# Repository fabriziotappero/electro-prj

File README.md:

# electronic projects
Bunch of electronics projects, pcb designs and embedded systems. All done in *KiCad*.

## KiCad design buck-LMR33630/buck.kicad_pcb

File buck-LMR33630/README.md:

This is a clever battery pack for a smartphone. It allows a 2S Sony NP battery 
to be interfaced with the standard USB-C port.

This pack includes a 5V, 3A Buck DC/DC Converter based on the TI LMR33630 and
a 19V, 2A step up converter based on the TI LM62421 as well.

The charging IC is the 

For any enquiry contact:

    fabrizio.tappero@gmail.com

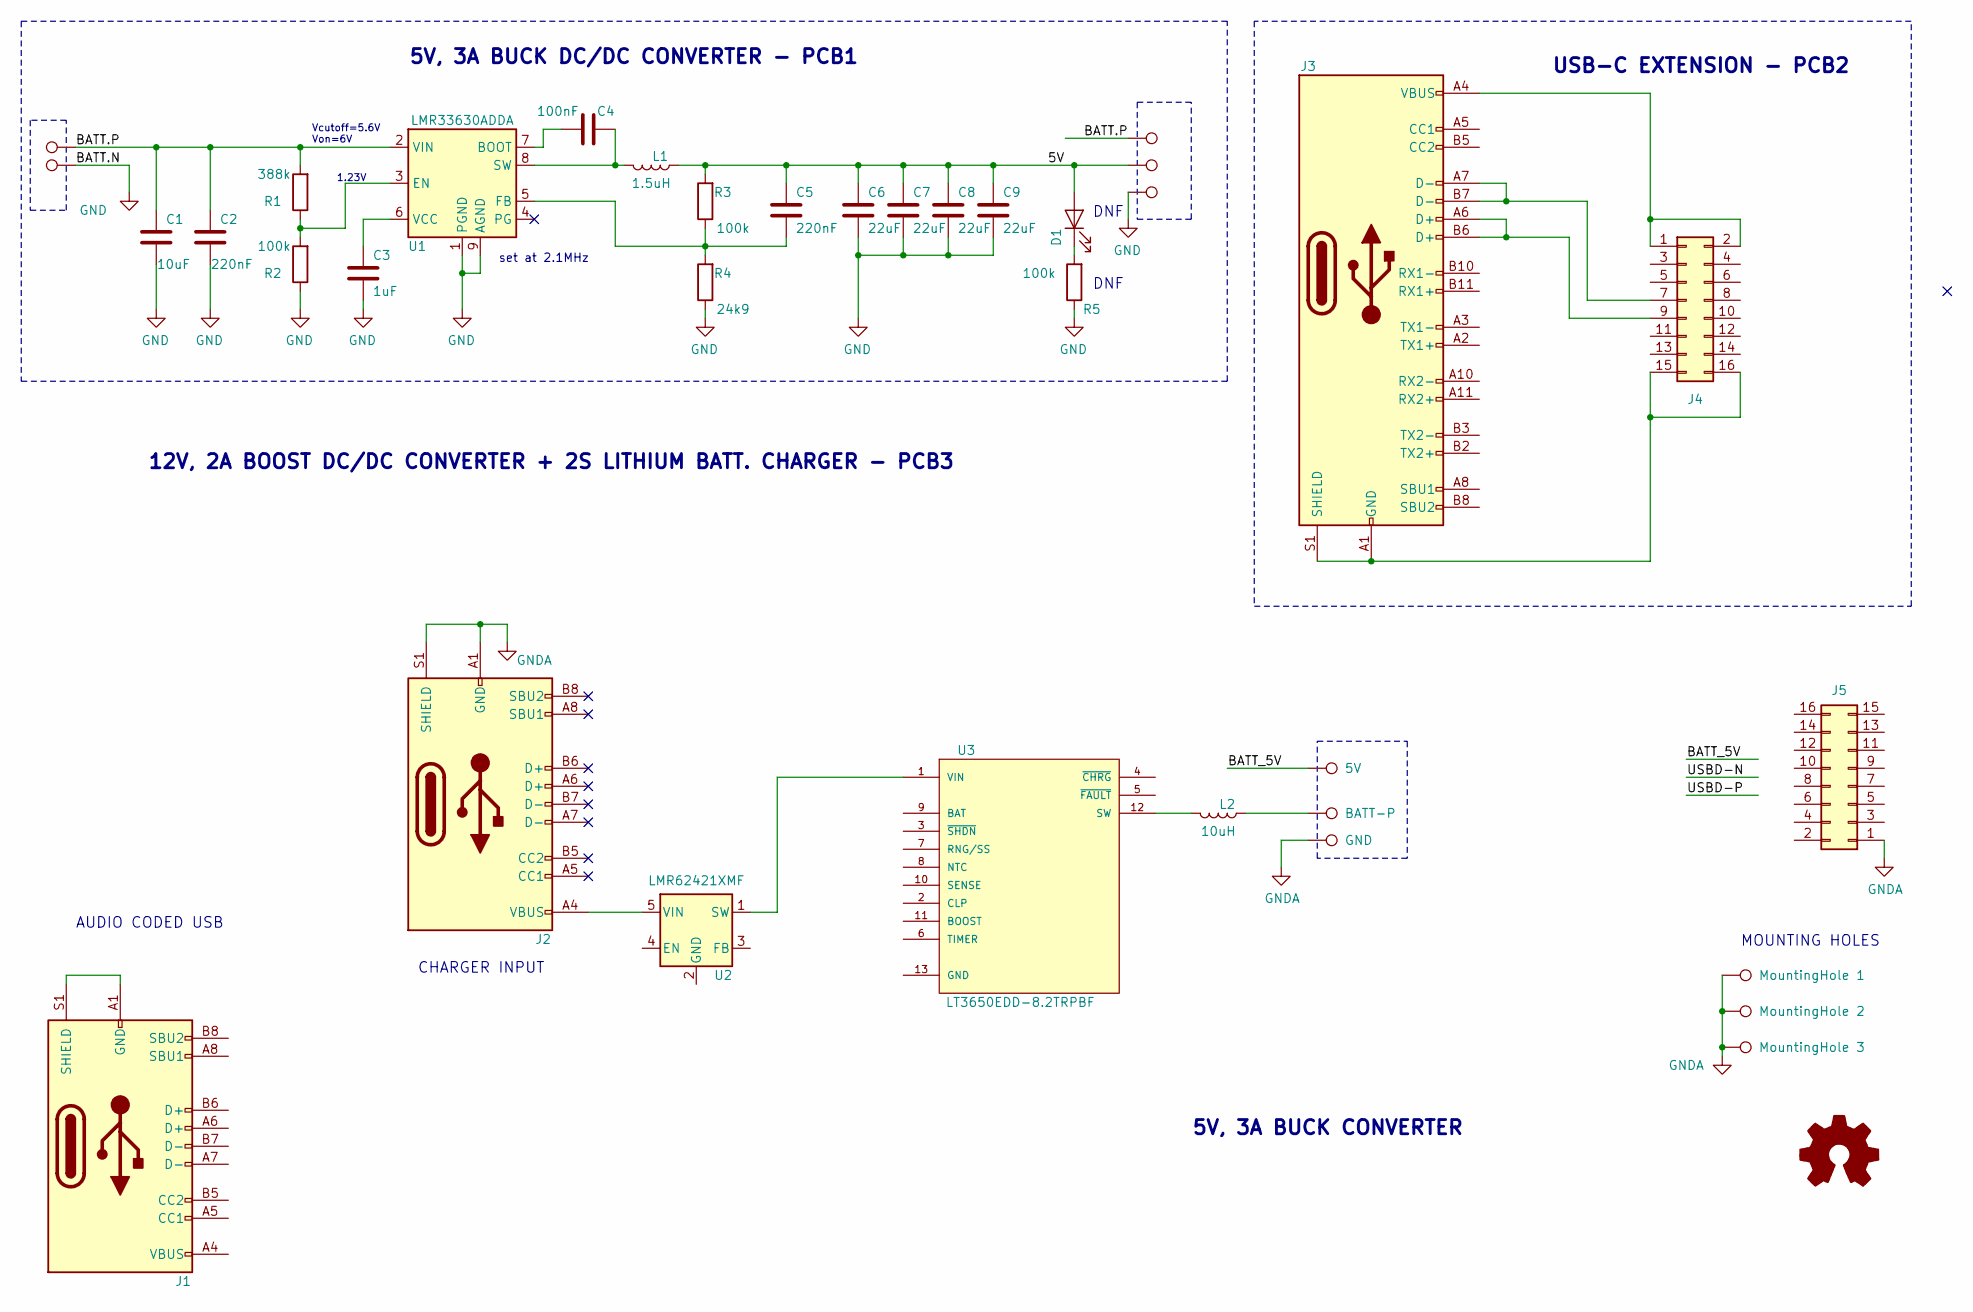
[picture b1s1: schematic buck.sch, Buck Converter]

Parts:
C1: 10uF; C_0805_2012Metric_Pad1.15x1.40mm_HandSolder; MPN TMK212BBJ106MGHT; Digikey PN none
C2, C5: 220nF; C_0805_2012Metric_Pad1.15x1.40mm_HandSolder; MPN none; Digikey PN none
C3: 1uF; C_0805_2012Metric_Pad1.15x1.40mm_HandSolder; MPN none; Digikey PN none
C4: 100nF; C_0805_2012Metric_Pad1.15x1.40mm_HandSolder; MPN none; Digikey PN none
C6, C7, C8, C9: 22uF; C_1206_3216Metric; MPN TMK316BBJ226ML-T; Digikey PN none
D1: LED; LED_0805_2012Metric_Pad1.15x1.40mm_HandSolder; Mouser PN 710-150080RS75000; Digikey PN 732-4984-1-ND
H1: MountingHole 1; MountingHole_3.2mm_M3_Pad_Via; MPN none; Digikey PN none
H2: MountingHole 2; MountingHole_3.2mm_M3_Pad_Via; MPN none; Digikey PN none
H3: MountingHole 3; MountingHole_3.2mm_M3_Pad_Via; MPN none; Digikey PN none
J1, J2: USB-C Connector; USB_C_Receptacle_GCT_USB4085; MPN USB4085-GF-A; Digikey PN 2073-USB4085-GF-ACT-ND
J3: USB_C_Receptacle; USB_C_Plug_JAE_DX07P024AJ1
J4, J5: Conn_02x08_Odd_Even; PinHeader_2x08_P2.00mm_Vertical
L1: 1.5uH; L_Wuerth_MAPI-3020; MPN SRP3020TA-1R5M; Digikey PN none
L2: 10uH; L_Wuerth_MAPI-4030; MPN 74438357100; Digikey PN none
P1: BATT-P; TestPoint_THTPad_D3.0mm_Drill1.5mm; MPN none; Digikey PN none
P2: BATT-N; TestPoint_THTPad_D3.0mm_Drill1.5mm; MPN none; Digikey PN none
P3: GND; TestPoint_Pad_4.0x4.0mm; MPN none; Digikey PN none
P4: 5V; TestPoint_Pad_4.0x4.0mm; MPN none; Digikey PN none
P5: Pad BATT.P; TestPoint_Pad_4.0x4.0mm; MPN none; Digikey PN none
P6: Pad 5V; TestPoint_Pad_4.0x4.0mm; MPN none; Digikey PN none
P7: Pad GND; TestPoint_Pad_4.0x4.0mm; MPN none; Digikey PN none
P8: BATT-P; TestPoint_Pad_4.0x4.0mm; MPN none; Digikey PN none
R1: 388k; R_0805_2012Metric_Pad1.15x1.40mm_HandSolder; MPN none; Digikey PN none
R2, R3, R5: 100k; R_0805_2012Metric_Pad1.15x1.40mm_HandSolder; MPN none; Digikey PN none
R4: 24k9; R_0805_2012Metric_Pad1.15x1.40mm_HandSolder; MPN none; Digikey PN none
U1: LMR33630ADDA; Texas_HSOP-8-1EP_3.9x4.9mm_P1.27mm_ThermalVias; MPN LMR33630ADDAR; Digikey PN none
U2: LMR62421XMF; SOT-23-5
U3: LT3650EDD-8.2TRPBF; MSOP-12-1EP_3x4mm_P0.65mm_EP1.65x2.85mm_ThermalVias
logo1: Logo_Open_Hardware_Small; OSHW-Symbol_6.7x6mm_SilkScreen; MPN none; Digikey PN none

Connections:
/5V: C5.1, C6.1, C7.1, C8.1, C9.1, D1.2 (A), L1.1, P6.1, R3.2
/BATT.P: C1.1, C2.1, P1.1, P5.1, R1.2, U1.2 (VIN)
/BATT_5V: P4.1
GND: C1.2, C2.2, C3.2, C6.2, C7.2, C8.2, C9.2, P2.1, P7.1, R2.1, R4.1, R5.1, U1.1 (PGND), U1.9 (AGND)
GNDA: H1.1, H2.1, H3.1, J2.A1 (GND), J2.A12 (GND), J2.B1 (GND), J2.B12 (GND), J2.S1 (SHIELD), J5.1, P3.1
unnamed: C3.1, U1.6 (VCC)
unnamed: C4.1, U1.7 (BOOT)
unnamed: C4.2, L1.2, U1.8 (SW)
unnamed: C5.2, R3.1, R4.2, U1.5 (FB)
unnamed: D1.1 (K), R5.2
unnamed: J1.A1 (GND), J1.A12 (GND), J1.B1 (GND), J1.B12 (GND), J1.S1 (SHIELD)
unnamed: J1.A4 (VBUS), J1.A9 (VBUS), J1.B4 (VBUS), J1.B9 (VBUS)
unnamed: J2.A4 (VBUS), J2.A9 (VBUS), J2.B4 (VBUS), J2.B9 (VBUS), U2.5 (VIN)
unnamed: J3.A1 (GND), J3.A12 (GND), J3.B1 (GND), J3.B12 (GND), J3.S1 (SHIELD), J4.15, J4.16
unnamed: J3.A4 (VBUS), J3.A9 (VBUS), J3.B4 (VBUS), J3.B9 (VBUS), J4.1, J4.2
unnamed: J3.A6 (D+), J3.B6 (D+), J4.9
unnamed: J3.A7 (D-), J3.B7 (D-), J4.7
unnamed: L2.1, P8.1
unnamed: L2.2, U3.12 (SW)
unnamed: R1.1, R2.2, U1.3 (EN)
unnamed: U2.1 (SW), U3.1 (VIN)

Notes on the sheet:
5V, 3A BUCK CONVERTER
5V, 3A BUCK DC/DC CONVERTER - PCB1
set at 2.1MHz
1.23V
Vcutoff=5.6V Von=6V
12V, 2A BOOST DC/DC CONVERTER + 2S LITHIUM BATT. CHARGER - PCB3
DNF
MOUNTING HOLES
USB-C EXTENSION - PCB2
CHARGER INPUT
AUDIO CODED USB

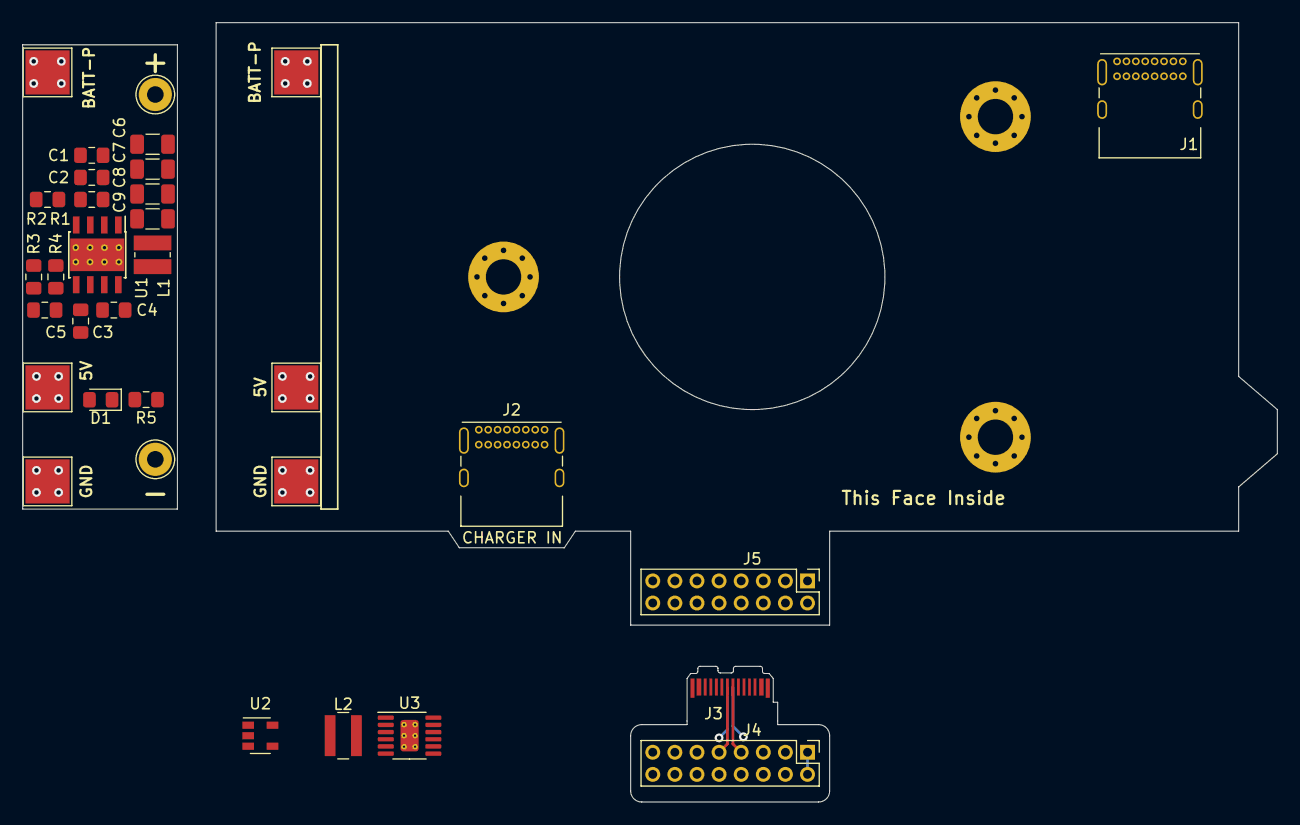
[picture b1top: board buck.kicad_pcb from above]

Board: 2 copper layers, 113.5 x 70.5 mm, 37 parts (1 on the bottom side), 20 nets.

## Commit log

2015-04-09 minor changes
2015-04-14 added few pdf docs
2015-04-16 buck-converter project now has a schematic and eagle lib components and few pdf
2015-04-16 added some pdf docs of some usb protection devices
2015-05-10 updated few pdf and buck schematic
2020-06-01 added a boost converter based in the LMR33630
2020-06-03 routed buck converter and added usb type c connector
2020-06-03 minor
2020-06-04 added lithium c2S charger and tried to route USB3... quite difficult
